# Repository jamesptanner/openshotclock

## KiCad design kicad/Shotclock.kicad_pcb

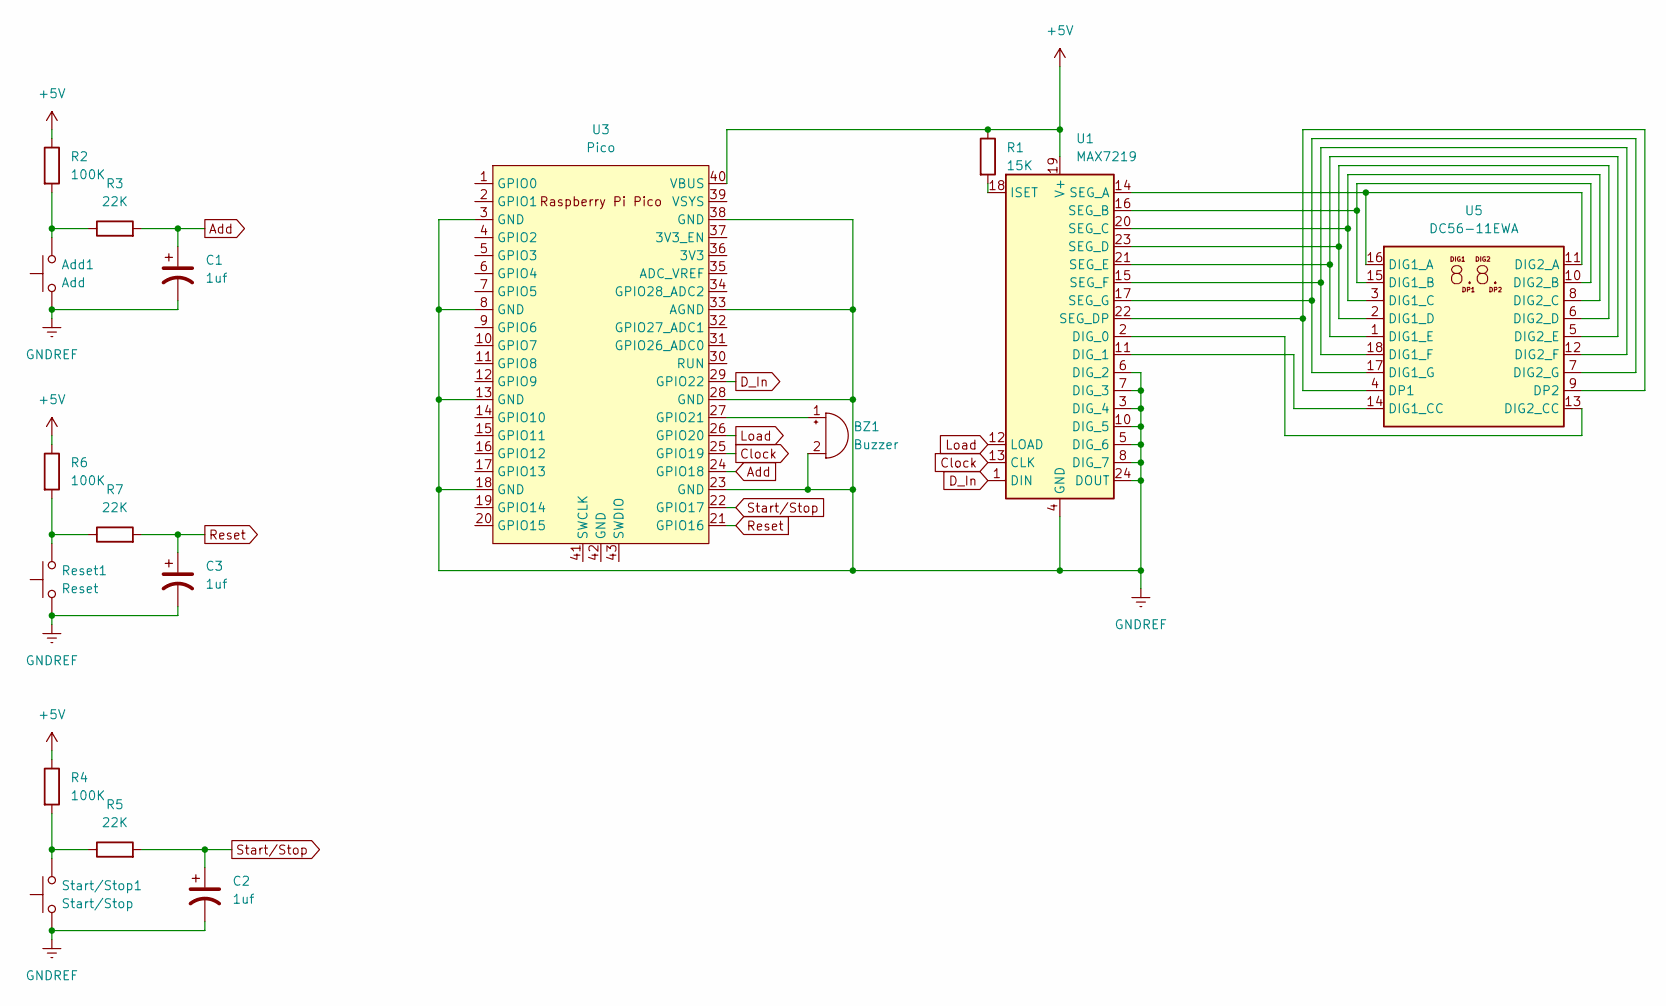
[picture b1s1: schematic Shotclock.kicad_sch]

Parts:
Add1: Add; SW_PUSH_6mm_H8mm
BZ1: Buzzer; Buzzer_12x9.5RM7.6
C1, C2, C3: 1uf; CP_Radial_Tantal_D5.0mm_P2.50mm
R1: 15K; R_Axial_DIN0204_L3.6mm_D1.6mm_P5.08mm_Horizontal
R2, R4, R6: 100K; R_Axial_DIN0204_L3.6mm_D1.6mm_P5.08mm_Horizontal
R3, R5, R7: 22K; R_Axial_DIN0204_L3.6mm_D1.6mm_P5.08mm_Horizontal
Reset1: Reset; SW_PUSH_6mm_H8mm
Start/Stop1: Start/Stop; SW_PUSH_6mm_H8mm
U1: MAX7219; DIP-24_W7.62mm_LongPads
U3: Pico; RPi_Pico_SMD_TH
U5: DC56-11EWA; DA56-11SURKWA

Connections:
+5V: R1.1, R2.1, R4.1, R6.1, U1.19 (V+), U3.40 (VBUS)
Add: C1.1, R3.2, U3.24 (GPIO18)
Clock: U1.13 (CLK), U3.25 (GPIO19)
D_In: U1.1 (DIN), U3.29 (GPIO22)
GNDREF: Add1.1, BZ1.2 (+), C1.2, C2.2, C3.2, Reset1.1, Start/Stop1.1, U1.3 (DIG_4), U1.4 (GND), U1.5 (DIG_6), U1.6 (DIG_2), U1.7 (DIG_3), U1.8 (DIG_7), U1.9 (GND), U1.10 (DIG_5), U1.24 (DOUT), U3.3 (GND), U3.8 (GND), U3.13 (GND), U3.18 (GND), U3.23 (GND), U3.28 (GND), U3.33 (AGND), U3.38 (GND)
Load: U1.12 (LOAD), U3.26 (GPIO20)
unnamed: Add1.2, R2.2, R3.1
unnamed: BZ1.1 (-), U3.27 (GPIO21)
unnamed: R4.2, R5.1, Start/Stop1.2
unnamed: R6.2, R7.1, Reset1.2
unnamed: U1.2 (DIG_0), U5.13 (DIG2_CC)
unnamed: U1.11 (DIG_1), U5.14 (DIG1_CC)
unnamed: R1.2, U1.18 (ISET)
unnamed: U1.14 (SEG_A), U5.11 (DIG2_A), U5.16 (DIG1_A)
unnamed: U1.16 (SEG_B), U5.10 (DIG2_B), U5.15 (DIG1_B)
unnamed: U1.20 (SEG_C), U5.3 (DIG1_C), U5.8 (DIG2_C)
unnamed: U1.23 (SEG_D), U5.2 (DIG1_D), U5.6 (DIG2_D)
unnamed: U1.22 (SEG_DP), U5.4 (DP1), U5.9 (DP2)
unnamed: U1.21 (SEG_E), U5.1 (DIG1_E), U5.5 (DIG2_E)
unnamed: U1.15 (SEG_F), U5.12 (DIG2_F), U5.18 (DIG1_F)
unnamed: U1.17 (SEG_G), U5.7 (DIG2_G), U5.17 (DIG1_G)
Reset: C3.1, R7.2, U3.21 (GPIO16)
Start/Stop: C2.1, R5.2, U3.22 (GPIO17)

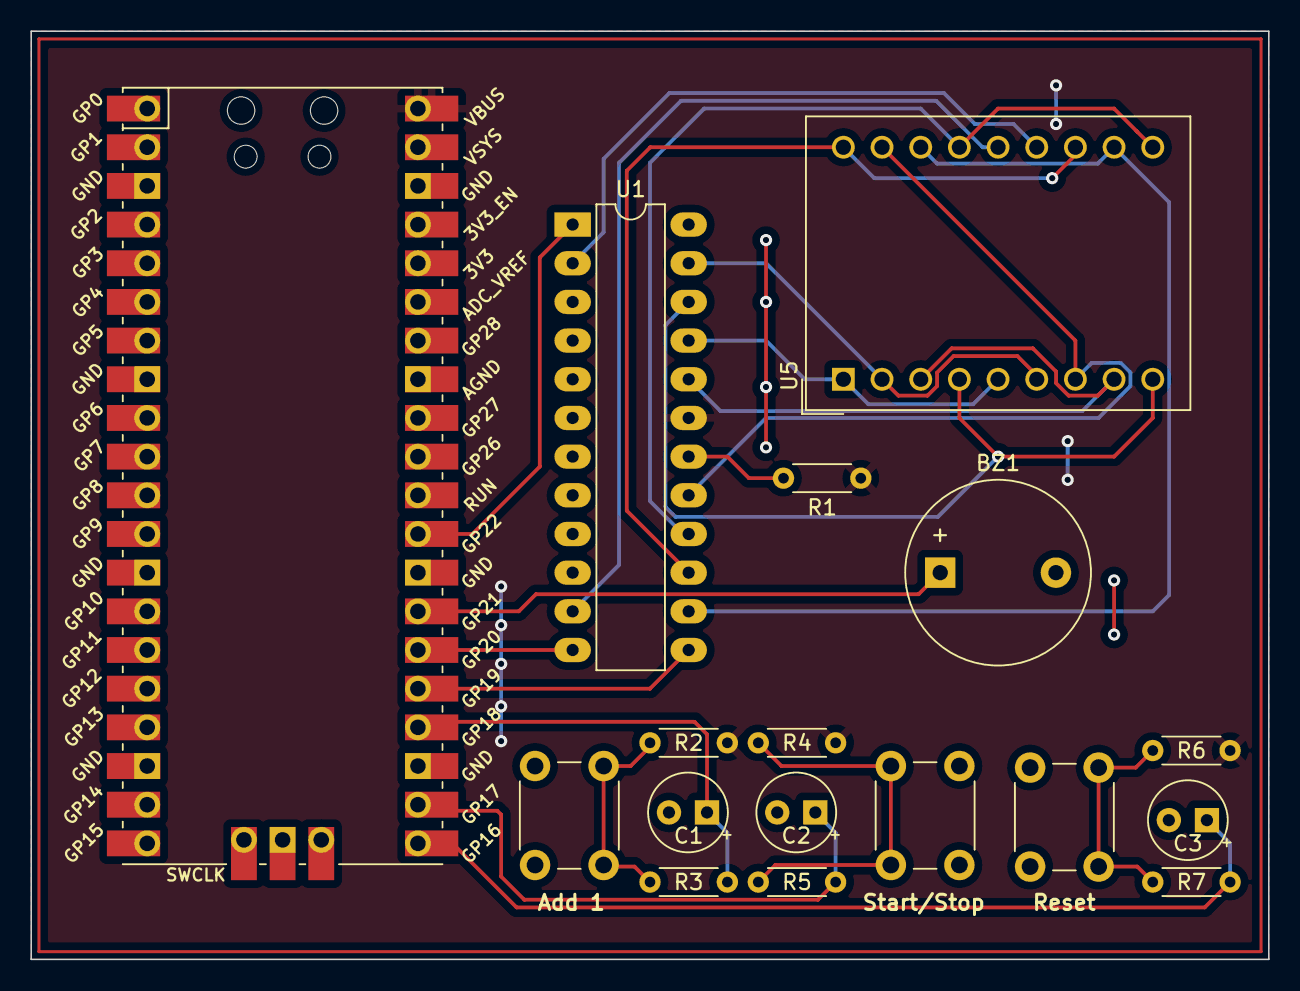
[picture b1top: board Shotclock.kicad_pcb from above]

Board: 2 copper layers, 81.3 x 61.0 mm, 17 parts (0 on the bottom side), 23 nets.

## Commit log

2024-02-28 Inital Code for pico_w
2024-02-28 First board design
2024-02-28 Set Defines for breadboard version of shotclock.
2024-02-29 fix the shutdown cmd.
2024-03-03 Begin preparing the countdown
2024-03-03 tidy up setup and begin work on clock functions.
2024-03-04 update to kikad8
2024-03-04 update ignore
2024-03-04 Shotclock mostly working. Need to double check the edge cases + start/stop.
2024-03-09 Add debouncing on startup and drive the buzzer
2024-03-10 add some software debouncing just in case.
2024-03-10 Fix timer pausing backwards.
